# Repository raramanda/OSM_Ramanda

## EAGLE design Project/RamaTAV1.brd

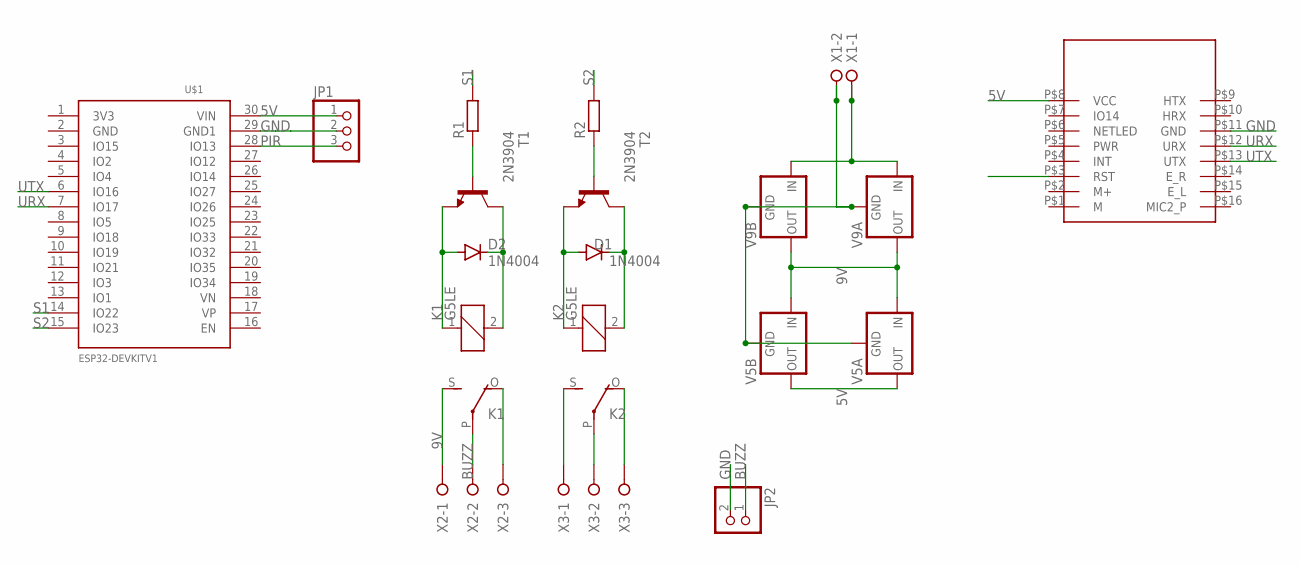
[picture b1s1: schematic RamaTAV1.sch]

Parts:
D1, D2: 1N4004; DO41-10
JP1: PINHD-1X3; 1X03
JP2: PINHD-1X2; 1X02
K1, K2: G5LE
R1, R2: R-EU_0207/10; 0207/10
T1, T2: 2N3904; TO92
U$1: ESP32DEVKITV1; ESP32-DEVKITV1
U$7: SIM_A6SIM_GA6; SIM_GA6
V5A, V5B, V9A, V9B: 78XXS
X1: W237-02P; W237-2
X2, X3: W237-03P; W237-3

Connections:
5V: JP1.1, U$1.30 (VIN), U$7.P$8 (VCC), V5A.OUT, V5B.OUT
9V: K1.S, V5A.IN, V5B.IN, V9A.OUT, V9B.OUT, X2.1
BUZZ: JP2.1, K1.P, X2.2
GND: JP1.2, JP2.2, U$1.29 (GND1), U$7.P$11 (GND)
unnamed: K1.O, X2.3
unnamed: K2.P, X3.2
unnamed: K2.O, X3.3
unnamed: K2.S, X3.1
unnamed: V5A.GND, V5B.GND, V9A.GND, V9B.GND, X1.2
unnamed: R1.1, T1.2 (B)
unnamed: V9A.IN, V9B.IN, X1.1
unnamed: R2.1, T2.2 (B)
unnamed: D2.A, K1.1, T1.3 (E)
unnamed: D2.C, K1.2, T1.1 (C)
unnamed: D1.A, K2.1, T2.3 (E)
unnamed: D1.C, K2.2, T2.1 (C)
PIR: JP1.3, U$1.28 (IO13)
S1: R1.2, U$1.14 (IO22)
S2: R2.2, U$1.15 (IO23)
URX: U$1.7 (IO17), U$7.P$12 (URX)
UTX: U$1.6 (IO16), U$7.P$13 (UTX)

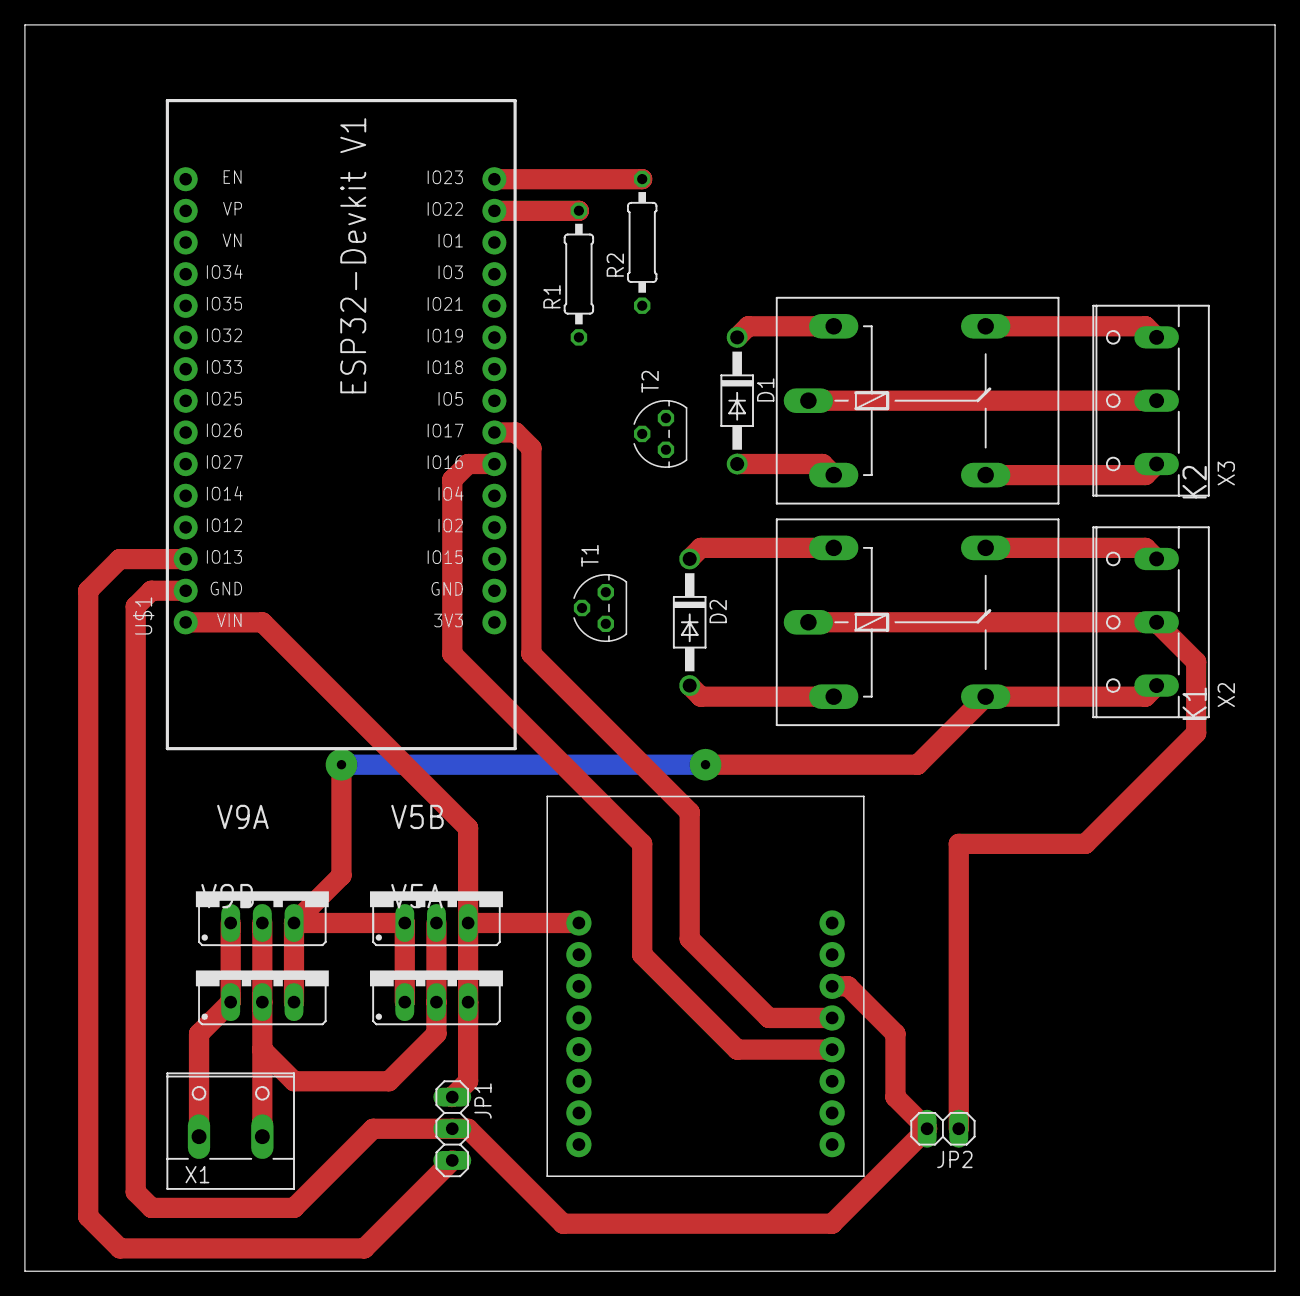
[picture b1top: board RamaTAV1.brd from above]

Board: 2 copper layers, 100.3 x 100.0 mm, 19 parts (0 on the bottom side), 21 nets.

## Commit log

2021-01-05 Menambahkan File-File Project PCB
